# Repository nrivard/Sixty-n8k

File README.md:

# Sixty-n8k
A Motorola 68000 SBC

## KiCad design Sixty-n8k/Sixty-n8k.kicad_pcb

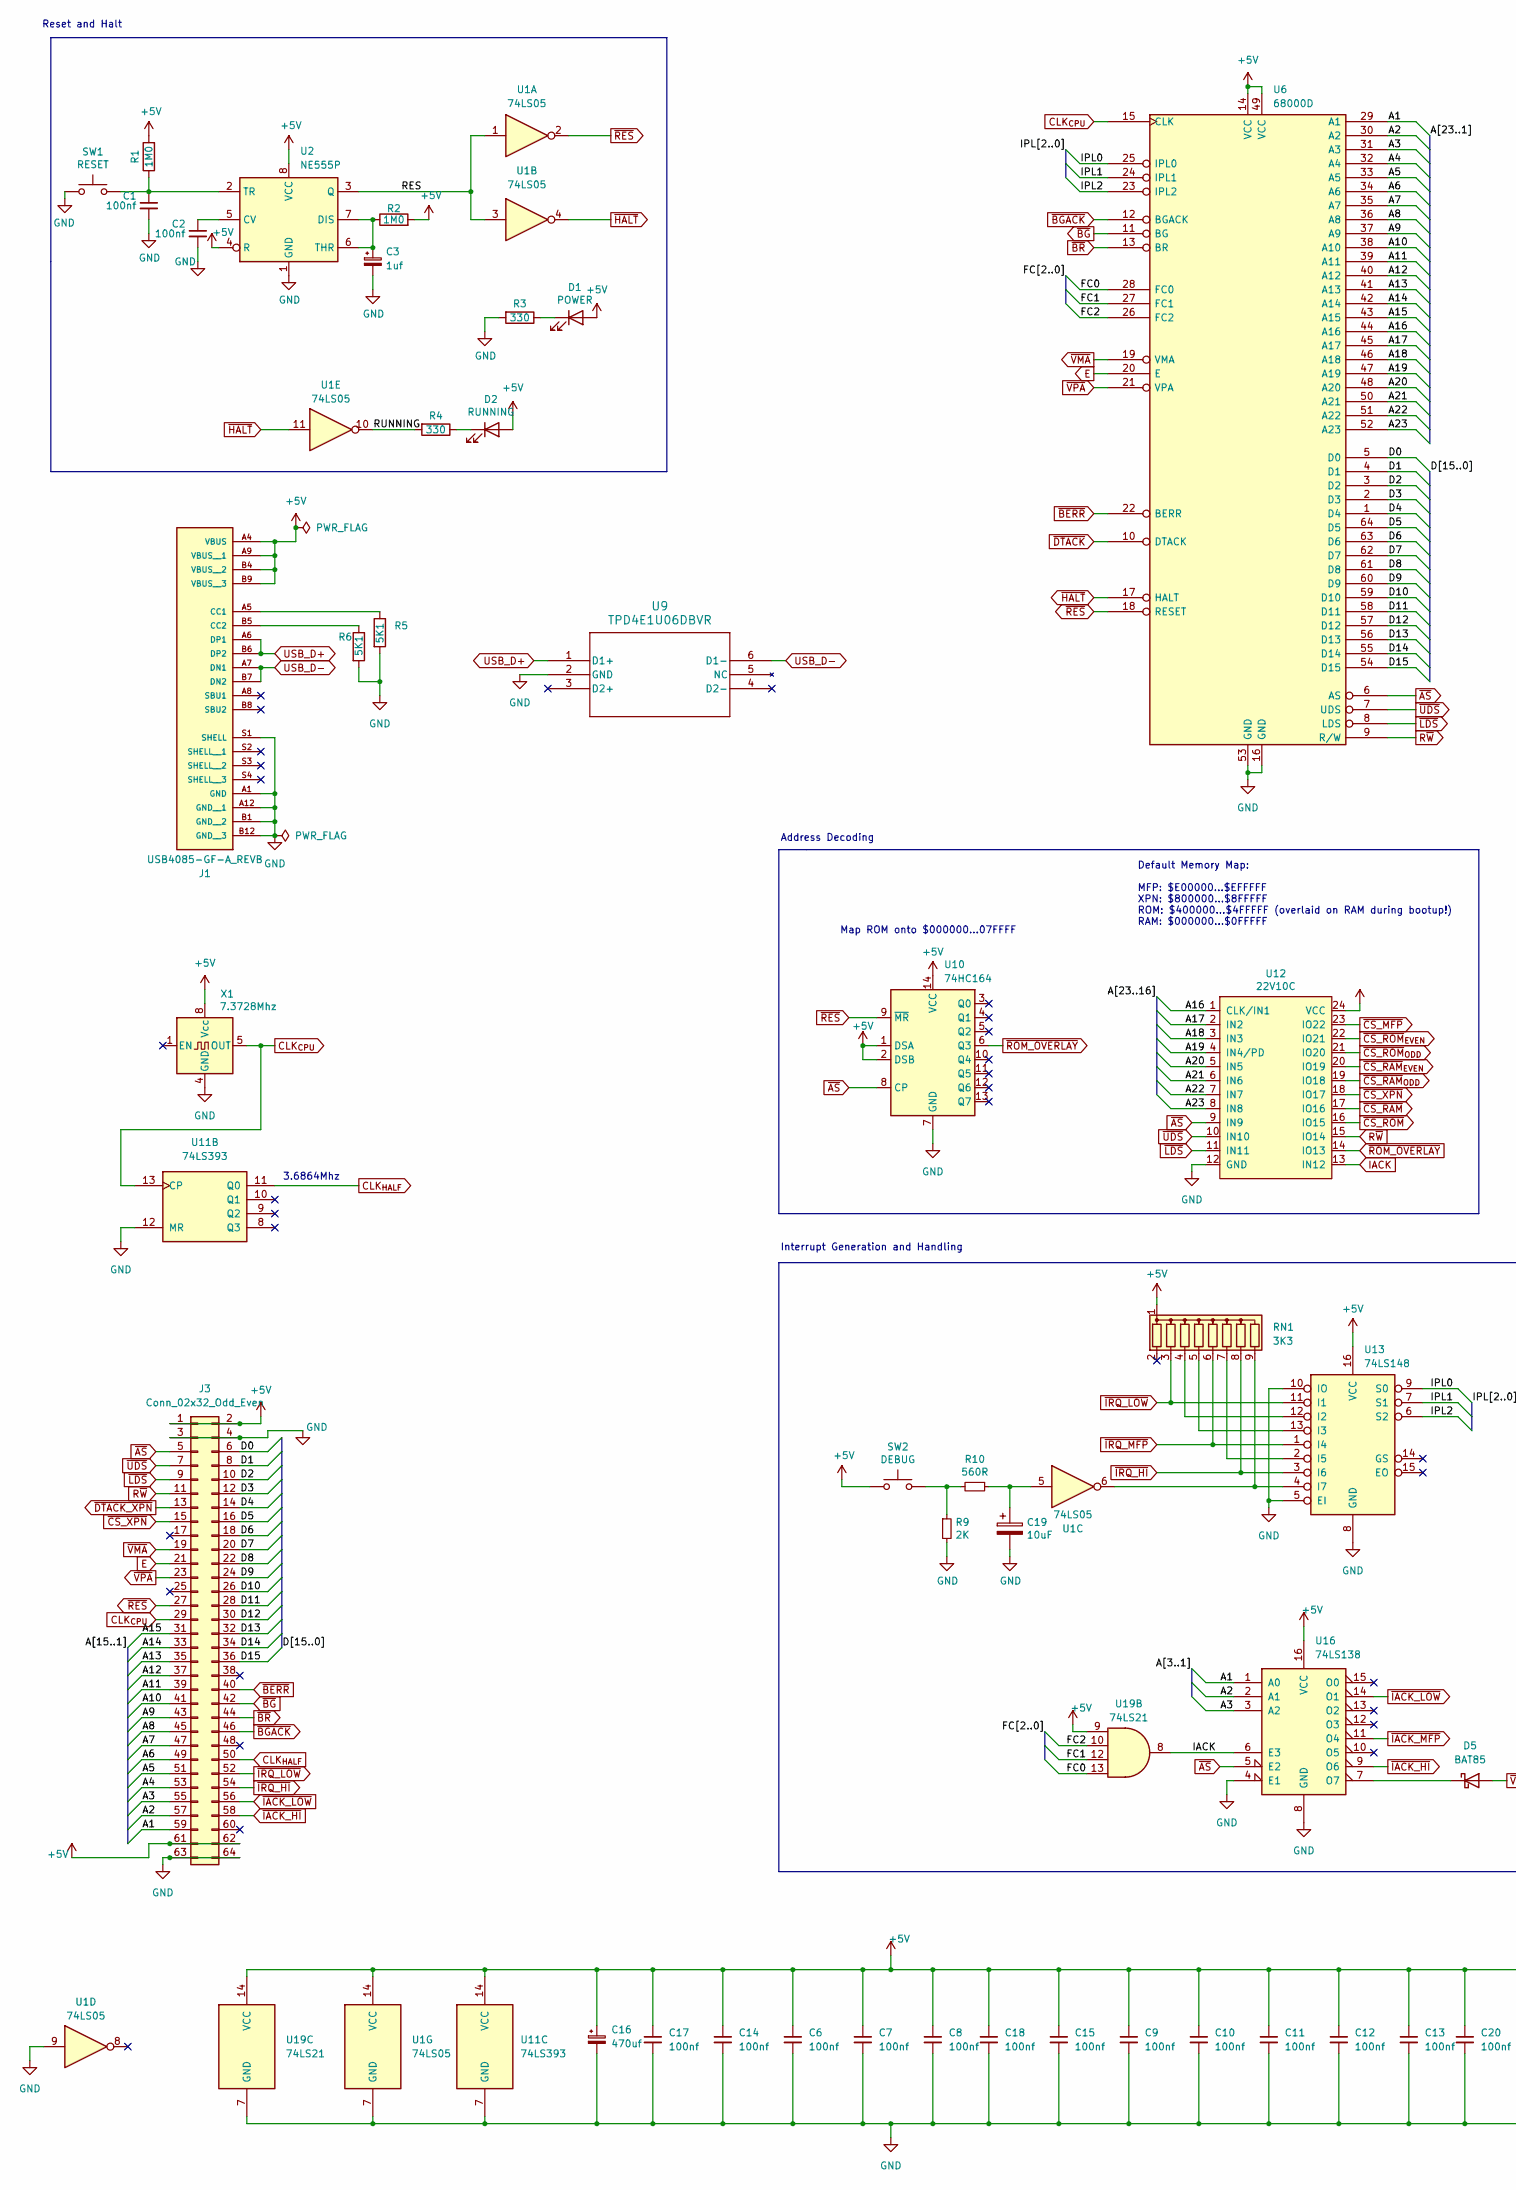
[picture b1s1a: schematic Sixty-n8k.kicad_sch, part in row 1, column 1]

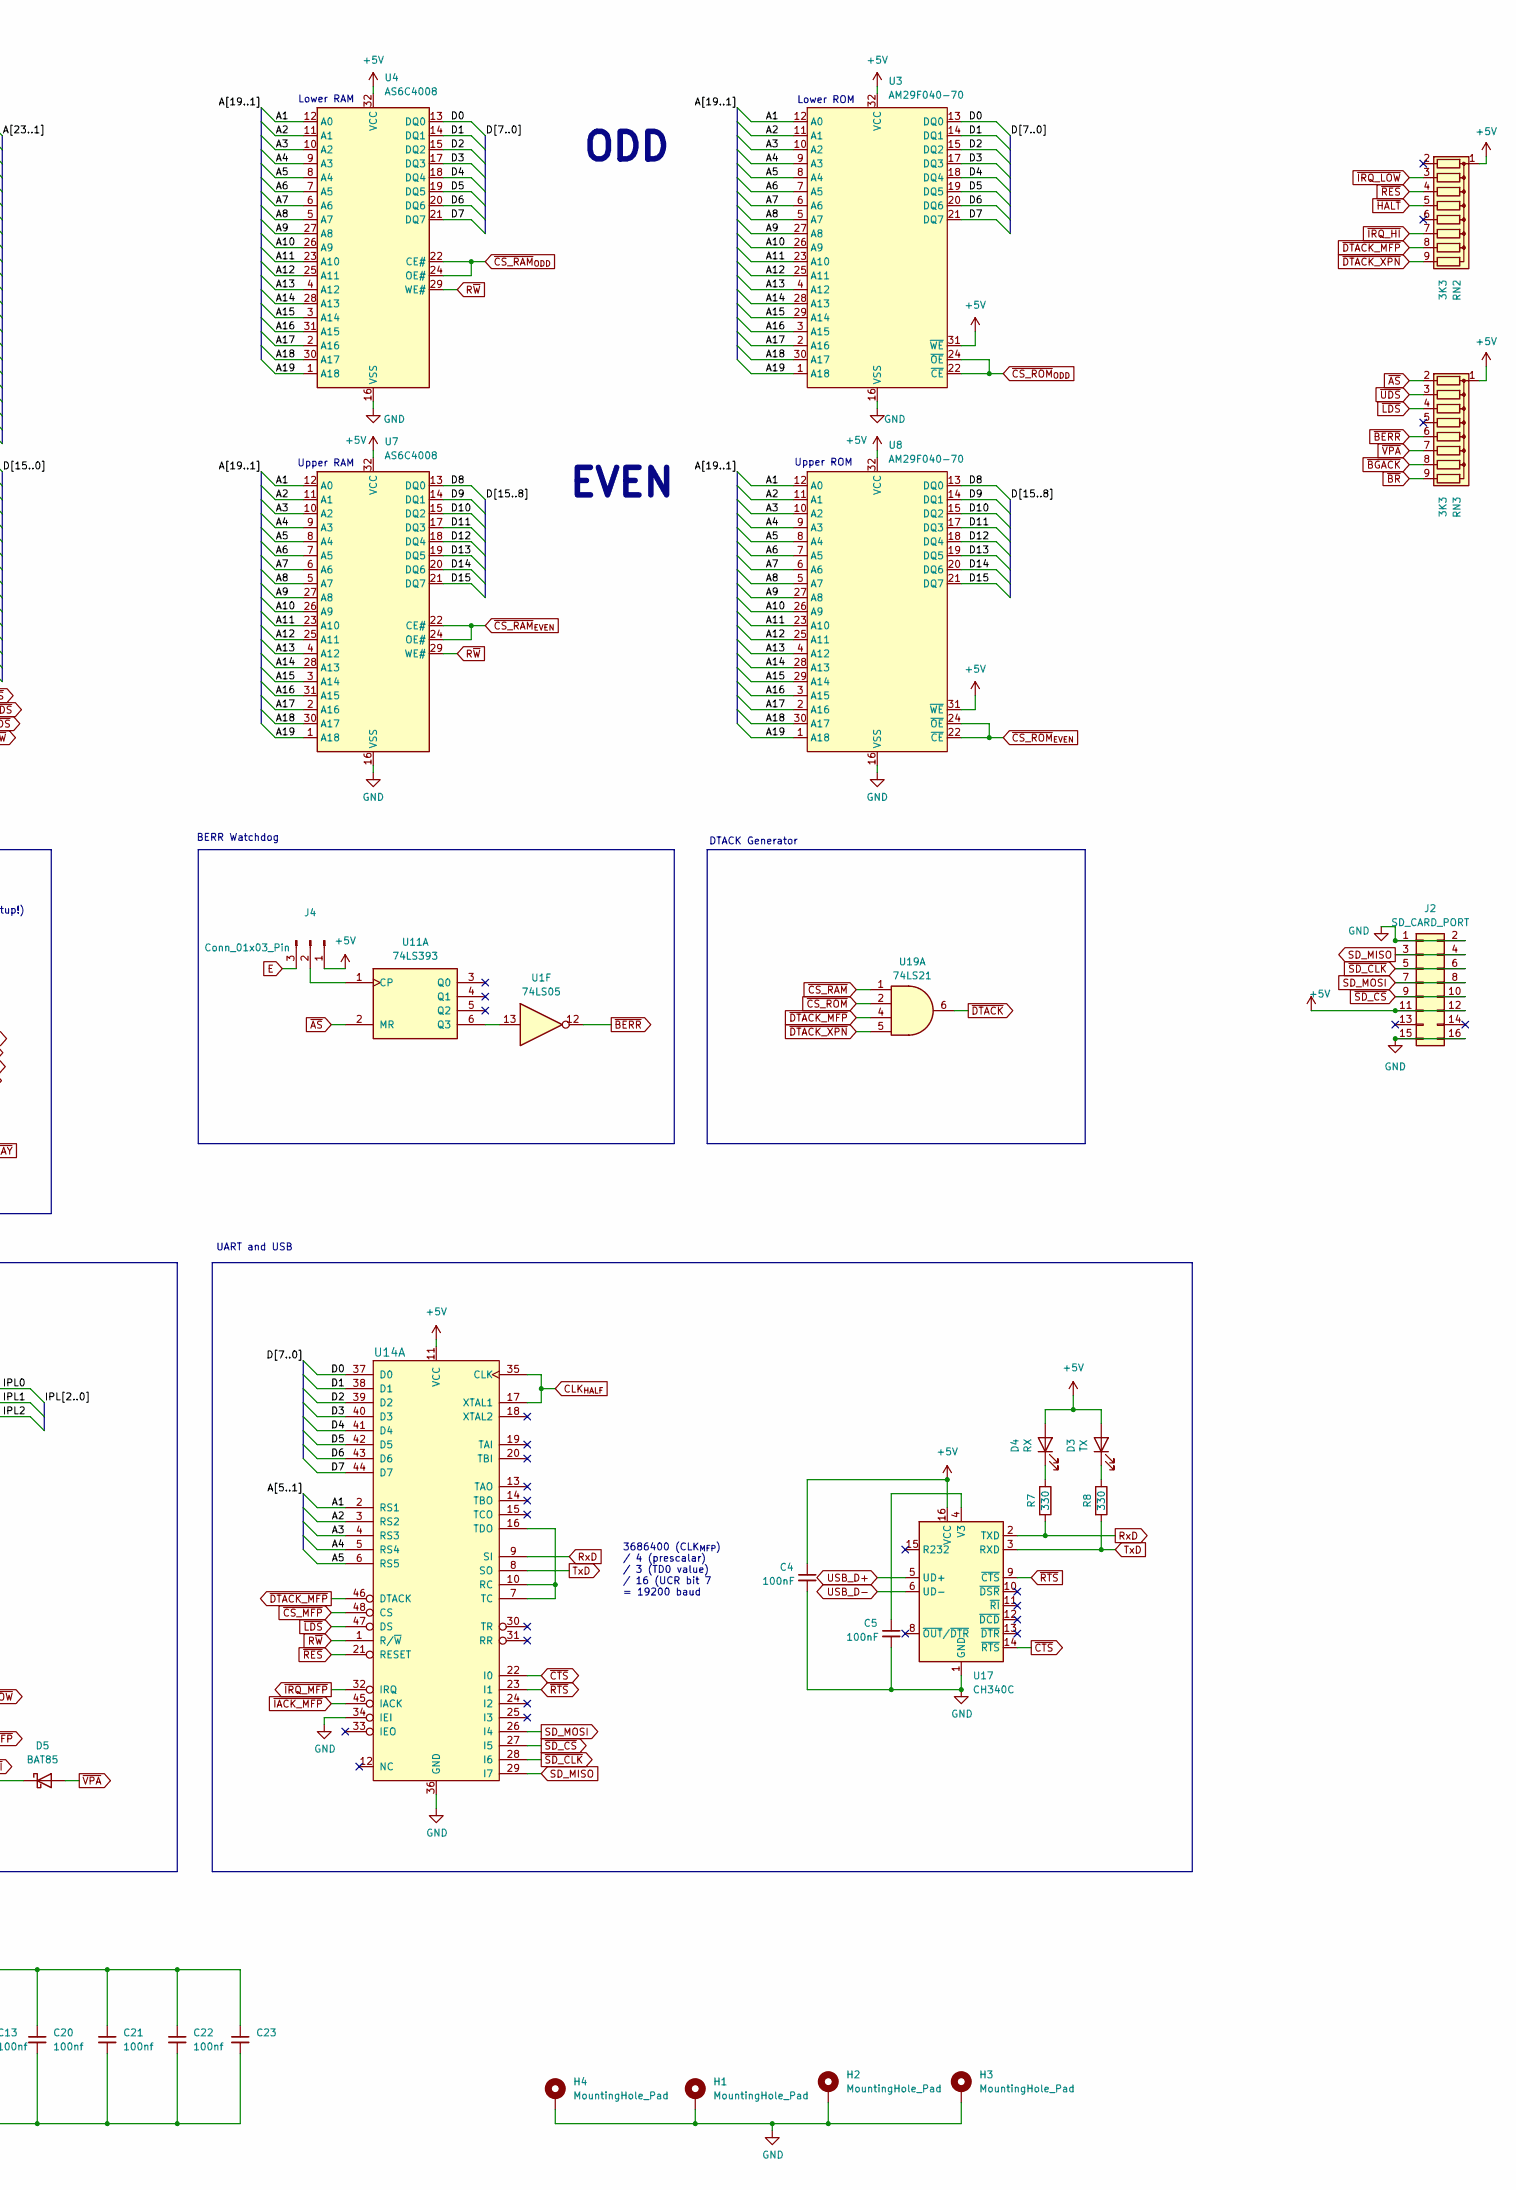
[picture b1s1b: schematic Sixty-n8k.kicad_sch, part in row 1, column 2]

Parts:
C1, C2, C6, C7, C8, C9, C10, C11, C12, C13, C14, C15, C17, C18, C20, C21, C22, C23: 100nf; C_Disc_D5.0mm_W2.5mm_P2.50mm
C3: 1uf; CP_Radial_D4.0mm_P2.00mm
C4, C5: 100nF; C_Disc_D5.0mm_W2.5mm_P2.50mm
C16: 470uf; CP_Radial_D8.0mm_P3.80mm
C19: 10uF; CP_Radial_D4.0mm_P2.00mm
D1: POWER; LED_D3.0mm
D2: RUNNING; LED_D3.0mm
D3: TX; LED_D3.0mm
D4: RX; LED_D3.0mm
D5: BAT85; D_DO-41_SOD81_P7.62mm_Horizontal
H1, H2, H3, H4: MountingHole_Pad; MountingHole_3.2mm_M3_DIN965_Pad
J1: USB4085-GF-A_REVB; GCT_USB4085-GF-A_REVB; PARTREV B
J2: SD_CARD_PORT; PinSocket_2x08_P2.54mm_Vertical
J3: Conn_02x32_Odd_Even; PinSocket_2x32_P2.54mm_Vertical
J4: Conn_01x03_Pin; PinHeader_1x03_P2.54mm_Vertical
R1, R2: 1M0; R_Axial_DIN0207_L6.3mm_D2.5mm_P7.62mm_Horizontal
R3, R4, R7, R8: 330; R_Axial_DIN0207_L6.3mm_D2.5mm_P7.62mm_Horizontal
R5, R6: 5K1; R_Axial_DIN0207_L6.3mm_D2.5mm_P7.62mm_Horizontal
R9: 2K; R_Axial_DIN0207_L6.3mm_D2.5mm_P7.62mm_Horizontal
R10: 560R; R_Axial_DIN0207_L6.3mm_D2.5mm_P7.62mm_Horizontal
RN1, RN2, RN3: 3K3; R_Array_SIP9
SW1: RESET; SW_PUSH-12mm
SW2: DEBUG; SW_PUSH-12mm
U1: 74LS05; DIP-14_W7.62mm_Socket
U2: NE555P; DIP-8_W7.62mm
U3, U8: AM29F040-70; PLCC-32_THT-Socket
U4, U7: AS6C4008; DIP-32_W15.24mm_Socket
U6: 68000D; DIP-64_W22.86mm_Socket
U9: TPD4E1U06DBVR; SOT-23-6_Handsoldering
U10: 74HC164; DIP-14_W7.62mm_Socket
U11: 74LS393; DIP-14_W7.62mm_Socket
U12: 22V10C; DIP-24_W7.62mm_Socket
U13: 74LS148; DIP-16_W7.62mm_Socket
U14: MC68901P; DIP-48_W15.24mm_Socket
U16: 74LS138; DIP-16_W7.62mm_Socket
U17: CH340C; SOIC-16_3.9x9.9mm_P1.27mm
U19: 74LS21; DIP-14_W7.62mm_Socket
X1: 7.3728Mhz; Oscillator_DIP-8

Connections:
+5V: C4.1, C6.1, C7.1, C8.1, C9.1, C10.1, C11.1, C12.1, C13.1, C14.1, C15.1, C16.1, C17.1, C18.1, C20.1, C21.1, C22.1, C23.1, D1.2 (A), D2.2 (A), D3.2 (A), D4.2 (A), J1.A4 (VBUS), J1.A9 (VBUS__1), J1.B4 (VBUS__2), J1.B9 (VBUS__3), J2.11, J2.12, J3.1, J3.2, J3.61, J3.62, J4.1, R1.2, R2.2, RN1.1 (common), RN2.1 (common), RN3.1 (common), SW2.1, U1.14 (VCC), U2.4 (R), U2.8 (VCC), U3.31 (~WE), U3.32 (VCC), U4.32 (VCC), U6.14 (VCC), U6.49 (VCC), U7.32 (VCC), U8.31 (~WE), U8.32 (VCC), U10.1 (DSA), U10.2 (DSB), U10.14 (VCC), U11.14 (VCC), U12.24 (VCC), U13.16 (VCC), U14.11 (VCC), U16.16 (VCC), U17.16 (VCC), U19.9, U19.14 (VCC), X1.8 (Vcc)
/A1: J3.59, U3.12 (A0), U4.12 (A0), U6.29 (A1), U7.12 (A0), U8.12 (A0), U14.2 (RS1), U16.1 (A0)
/A2: J3.57, U3.11 (A1), U4.11 (A1), U6.30 (A2), U7.11 (A1), U8.11 (A1), U14.3 (RS2), U16.2 (A1)
/A3: J3.55, U3.10 (A2), U4.10 (A2), U6.31 (A3), U7.10 (A2), U8.10 (A2), U14.4 (RS3), U16.3 (A2)
/A4: J3.53, U3.9 (A3), U4.9 (A3), U6.32 (A4), U7.9 (A3), U8.9 (A3), U14.5 (RS4)
/A5: J3.51, U3.8 (A4), U4.8 (A4), U6.33 (A5), U7.8 (A4), U8.8 (A4), U14.6 (RS5)
/A6: J3.49, U3.7 (A5), U4.7 (A5), U6.34 (A6), U7.7 (A5), U8.7 (A5)
/A7: J3.47, U3.6 (A6), U4.6 (A6), U6.35 (A7), U7.6 (A6), U8.6 (A6)
/A8: J3.45, U3.5 (A7), U4.5 (A7), U6.36 (A8), U7.5 (A7), U8.5 (A7)
/A9: J3.43, U3.27 (A8), U4.27 (A8), U6.37 (A9), U7.27 (A8), U8.27 (A8)
/A10: J3.41, U3.26 (A9), U4.26 (A9), U6.38 (A10), U7.26 (A9), U8.26 (A9)
/A11: J3.39, U3.23 (A10), U4.23 (A10), U6.39 (A11), U7.23 (A10), U8.23 (A10)
/A12: J3.37, U3.25 (A11), U4.25 (A11), U6.40 (A12), U7.25 (A11), U8.25 (A11)
/A13: J3.35, U3.4 (A12), U4.4 (A12), U6.41 (A13), U7.4 (A12), U8.4 (A12)
/A14: J3.33, U3.28 (A13), U4.28 (A13), U6.42 (A14), U7.28 (A13), U8.28 (A13)
/A15: J3.31, U3.29 (A14), U4.3 (A14), U6.43 (A15), U7.3 (A14), U8.29 (A14)
/A16: U3.3 (A15), U4.31 (A15), U6.44 (A16), U7.31 (A15), U8.3 (A15), U12.1 (CLK/IN1)
/A17: U3.2 (A16), U4.2 (A16), U6.45 (A17), U7.2 (A16), U8.2 (A16), U12.2 (IN2)
/A18: U3.30 (A17), U4.30 (A17), U6.46 (A18), U7.30 (A17), U8.30 (A17), U12.3 (IN3)
/A19: U3.1 (A18), U4.1 (A18), U6.47 (A19), U7.1 (A18), U8.1 (A18), U12.4 (IN4/PD)
/A20: U6.48 (A20), U12.5 (IN5)
/A21: U6.50 (A21), U12.6 (IN6)
/A22: U6.51 (A22), U12.7 (IN7)
/A23: U6.52 (A23), U12.8 (IN8)
/D0: J3.6, U3.13 (DQ0), U4.13 (DQ0), U6.5 (D0), U14.37 (D0)
/D1: J3.8, U3.14 (DQ1), U4.14 (DQ1), U6.4 (D1), U14.38 (D1)
/D2: J3.10, U3.15 (DQ2), U4.15 (DQ2), U6.3 (D2), U14.39 (D2)
/D3: J3.12, U3.17 (DQ3), U4.17 (DQ3), U6.2 (D3), U14.40 (D3)
/D4: J3.14, U3.18 (DQ4), U4.18 (DQ4), U6.1 (D4), U14.41 (D4)
/D5: J3.16, U3.19 (DQ5), U4.19 (DQ5), U6.64 (D5), U14.42 (D5)
/D6: J3.18, U3.20 (DQ6), U4.20 (DQ6), U6.63 (D6), U14.43 (D6)
/D7: J3.20, U3.21 (DQ7), U4.21 (DQ7), U6.62 (D7), U14.44 (D7)
/D8: J3.22, U6.61 (D8), U7.13 (DQ0), U8.13 (DQ0)
/D9: J3.24, U6.60 (D9), U7.14 (DQ1), U8.14 (DQ1)
/D10: J3.26, U6.59 (D10), U7.15 (DQ2), U8.15 (DQ2)
/D11: J3.28, U6.58 (D11), U7.17 (DQ3), U8.17 (DQ3)
/D12: J3.30, U6.57 (D12), U7.18 (DQ4), U8.18 (DQ4)
/D13: J3.32, U6.56 (D13), U7.19 (DQ5), U8.19 (DQ5)
/D14: J3.34, U6.55 (D14), U7.20 (DQ6), U8.20 (DQ6)
/D15: J3.36, U6.54 (D15), U7.21 (DQ7), U8.21 (DQ7)
/FC0: U6.28 (FC0), U19.13
/FC1: U6.27 (FC1), U19.12
/FC2: U6.26 (FC2), U19.10
/IPL0: U6.25 (IPL0), U13.9 (S0)
/IPL1: U6.24 (IPL1), U13.7 (S1)
/IPL2: U6.23 (IPL2), U13.6 (S2)
/RES: U1.1, U1.3, U2.3 (Q)
/RUNNING: R4.2, U1.10
CLK_{CPU}: J3.29, U6.15 (CLK), U11.13 (CP), X1.5 (OUT)
CLK_{HALF}: J3.50, U11.11 (Q0), U14.17 (XTAL1), U14.35 (CLK)
E: J3.21, J4.3, U6.20 (E)
GND: C1.2, C2.2, C3.2, C4.2, C5.2, C6.2, C7.2, C8.2, C9.2, C10.2, C11.2, C12.2, C13.2, C14.2, C15.2, C16.2, C17.2, C18.2, C19.2, C20.2, C21.2, C22.2, C23.2, H1.1, H2.1, H3.1, H4.1, J1.A1 (GND), J1.A12 (GND__1), J1.B1 (GND__2), J1.B12 (GND__3), J1.S1 (SHELL), J2.1, J2.2, J2.15, J2.16, J3.3, J3.4, J3.63, J3.64, R3.2, R5.2, R6.2, R9.2, SW1.1, U1.7 (GND), U1.9, U2.1 (GND), U3.16 (VSS), U4.16 (VSS), U6.16 (GND), U6.53 (GND), U7.16 (VSS), U8.16 (VSS), U9.2 (GND), U10.7 (GND), U11.7 (GND), U11.12 (MR), U12.12 (GND), U13.5 (EI), U13.8 (GND), U13.10 (IO), U14.34 (IEI), U14.36 (GND), U16.4 (E1), U16.8 (GND), U17.1 (GND), U19.7 (GND), X1.4 (GND)
IACK: U12.13 (IN12), U16.6 (E3), U19.8
unnamed: C19.1, R10.1, U1.5
unnamed: D1.1 (K), R3.1
unnamed: D2.1 (K), R4.1
unnamed: D3.1 (K), R8.1
unnamed: D4.1 (K), R7.1
unnamed: D5.1 (K), U16.7 (O7)
unnamed: J1.A5 (CC1), R5.1
unnamed: J1.B5 (CC2), R6.1
unnamed: J4.2, U11.1 (CP)
unnamed: R9.1, R10.2, SW2.2
unnamed: RN1.4 (R3), U13.12 (I2)
unnamed: RN1.5 (R4), U13.13 (I3)
unnamed: RN1.7 (R6), U13.2 (I5)
unnamed: RN1.9 (R8), U1.6, U13.4 (I7)
unnamed: C2.1, U2.5 (CV)
unnamed: C3.1, R2.1, U2.6 (THR), U2.7 (DIS)
unnamed: C1.1, R1.1, SW1.2, U2.2 (TR)
unnamed: U1.13, U11.6 (Q3)
unnamed: U14.7 (TC), U14.10 (RC), U14.16 (TDO)
unnamed: C5.1, U17.4 (V3)
RxD: R7.2, U14.9 (SI), U17.2 (TXD)
R~W: J3.11, U4.29 (WE#), U6.9 (R/W), U7.29 (WE#), U12.15 (IO14), U14.1 (R/~W)
SD_MISO: J2.3, J2.4, U14.29 (I7)
SD_MOSI: J2.7, J2.8, U14.26 (I4)
TxD: R8.2, U14.8 (SO), U17.3 (RXD)
USB_D+: J1.A6 (DP1), J1.B6 (DP2), U9.1 (D1+), U17.5 (UD+)
USB_D-: J1.A7 (DN1), J1.B7 (DN2), U9.6 (D1-), U17.6 (UD-)
~AS: J3.5, RN3.2 (R1), U6.6 (AS), U10.8 (CP), U11.2 (MR), U12.9 (IN9), U16.5 (E2)
~BERR: J3.40, RN3.6 (R5), U1.12, U6.22 (BERR)
~BGACK: J3.46, RN3.8 (R7), U6.12 (BGACK)
~BG: J3.42, U6.11 (BG)
~BR: J3.44, RN3.9 (R8), U6.13 (BR)
~CS_MFP: U12.23 (IO22), U14.48 (CS)
~CS_RAM: U12.17 (IO16), U19.1
~CS_RAM_{EVEN}: U7.22 (CE#), U7.24 (OE#), U12.20 (IO19)
~CS_RAM_{ODD}: U4.22 (CE#), U4.24 (OE#), U12.19 (IO18)
~CS_ROM: U12.16 (IO15), U19.2
~CS_ROM_{EVEN}: U8.22 (~CE), U8.24 (~OE), U12.22 (IO21)
~CS_ROM_{ODD}: U3.22 (~CE), U3.24 (~OE), U12.21 (IO20)
~CS_XPN: J3.15, U12.18 (IO17)
~CTS: U14.22 (I0), U17.14 (~RTS)
~DTACK_MFP: RN2.8 (R7), U14.46 (DTACK), U19.4
~DTACK_XPN: J3.13, RN2.9 (R8), U19.5
~DTACK: U6.10 (DTACK), U19.6
~HALT: RN2.5 (R4), U1.4, U1.11, U6.17 (HALT)
~IACK_HI: J3.58, U16.9 (O6)
~IACK_LOW: J3.56, U16.14 (O1)
~IACK_MFP: U14.45 (IACK), U16.11 (O4)
~IRQ_HI: J3.54, RN1.8 (R7), RN2.7 (R6), U13.3 (I6)
~IRQ_LOW: J3.52, RN1.3 (R2), RN2.3 (R2), U13.11 (I1)
~IRQ_MFP: RN1.6 (R5), U13.1 (I4), U14.32 (IRQ)
~LDS: J3.9, RN3.4 (R3), U6.8 (LDS), U12.11 (IN11), U14.47 (DS)
~RES: J3.27, RN2.4 (R3), U1.2, U6.18 (RESET), U10.9 (~MR), U14.21 (RESET)
~ROM_OVERLAY: U10.6 (Q3), U12.14 (IO13)
~RTS: U14.23 (I1), U17.9 (~CTS)
~SD_CLK: J2.5, J2.6, U14.28 (I6)
~SD_CS: J2.9, J2.10, U14.27 (I5)
~UDS: J3.7, RN3.3 (R2), U6.7 (UDS), U12.10 (IN10)
~VMA: J3.19, U6.19 (VMA)
~VPA: D5.2 (A), J3.23, RN3.7 (R6), U6.21 (VPA)

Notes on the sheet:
ODD
3686400 (CLK_{MFP}) / 4 (prescalar) / 3 (TD0 value) / 16 (UCR bit 7 = 19200 baud
Reset and Halt
DTACK Generator
EVEN
Map ROM onto $000000...07FFFF
3.6864Mhz
Default Memory Map: MFP: $E00000...$EFFFFF XPN: $800000...$8FFFFF ROM: $400000...$4FFFFF (overlaid on RAM during bootup!) RAM: $000000...$0FFFFF
Lower RAM
BERR Watchdog
Upper ROM
UART and USB
Upper RAM
Lower ROM
Interrupt Generation and Handling
Address Decoding

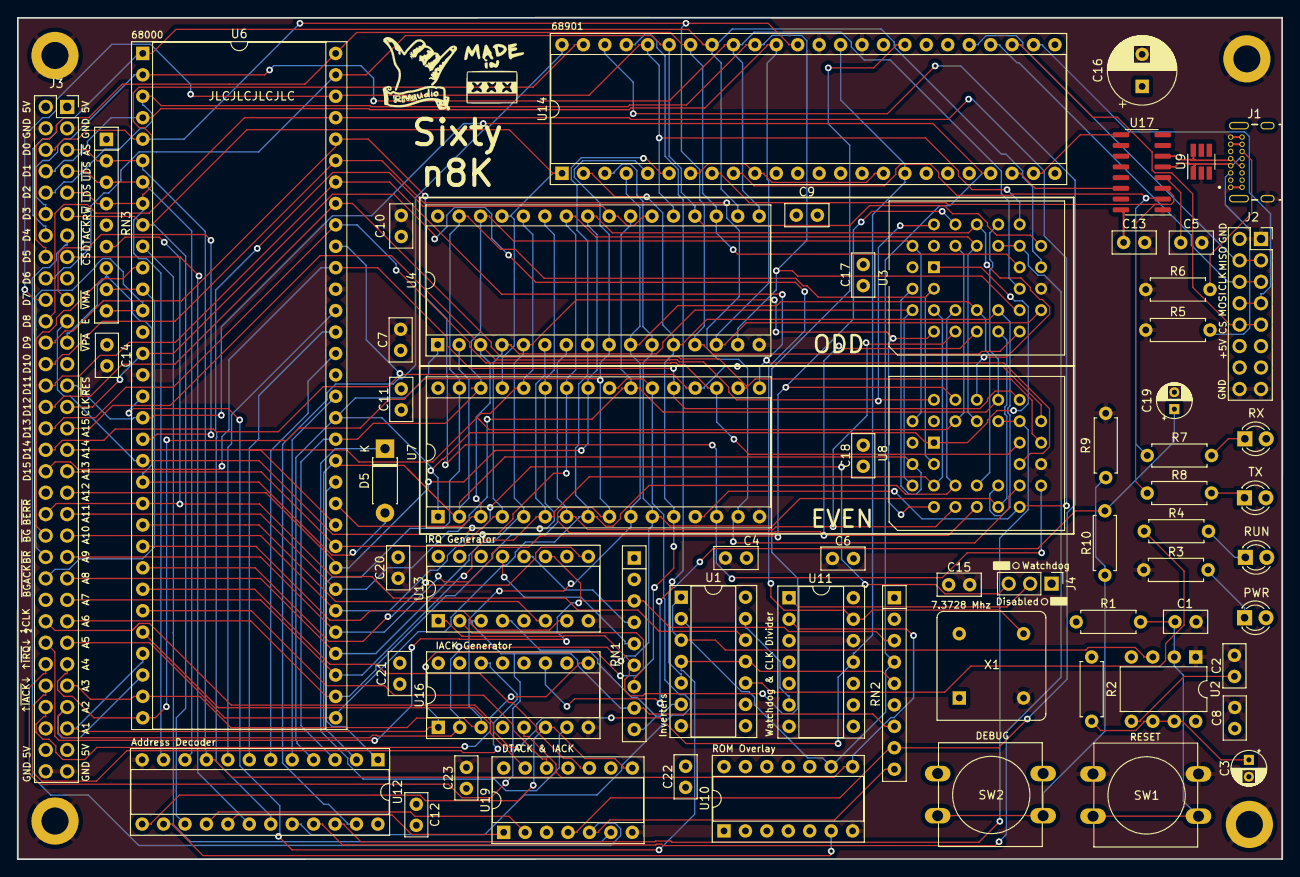
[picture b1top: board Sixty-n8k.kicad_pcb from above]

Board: 4 copper layers, 149.9 x 99.7 mm, 70 parts (0 on the bottom side), 113 nets.

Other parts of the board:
G1: LOGO; Shaka
G2: LOGO; MadeInAMS

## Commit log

2023-10-31 Start of schematic
    Uses 28L92 but I think for v1 i actually want to use 68901 MFP just like rosco 68k.
2023-11-29 Added MFP, IRQ handling, BERR watchdog, ROM overlay
2023-12-15 Schematic is complete (rc1)
2023-12-15 Starting to hand route. want to just layout and see what autorouter does though...
2023-12-18 new layout, start of hand routing but very complex
2023-12-19 Autoroute success (don't judge me)
2023-12-20 About to remove 2nd 74HC138
2023-12-21 Simplified design, relaid out, re-routed
2023-12-21 More sane layout and further reductions
2024-01-28 Adds GAL logic
2024-02-05 Formatting changes
2024-02-07 Removed pullup on RWb
2024-02-09 Sent to pcb board house
2024-02-10 Fixes a couple of small issues
2024-02-14 PCB cleanup
2024-02-23 footprint fix :(
2024-02-26 Fixed footprint issue
2024-03-01 Open collector via schottky diode for NMI
2024-03-01 Re-added logo
2024-03-06 Fixed short trace to CC resistor
